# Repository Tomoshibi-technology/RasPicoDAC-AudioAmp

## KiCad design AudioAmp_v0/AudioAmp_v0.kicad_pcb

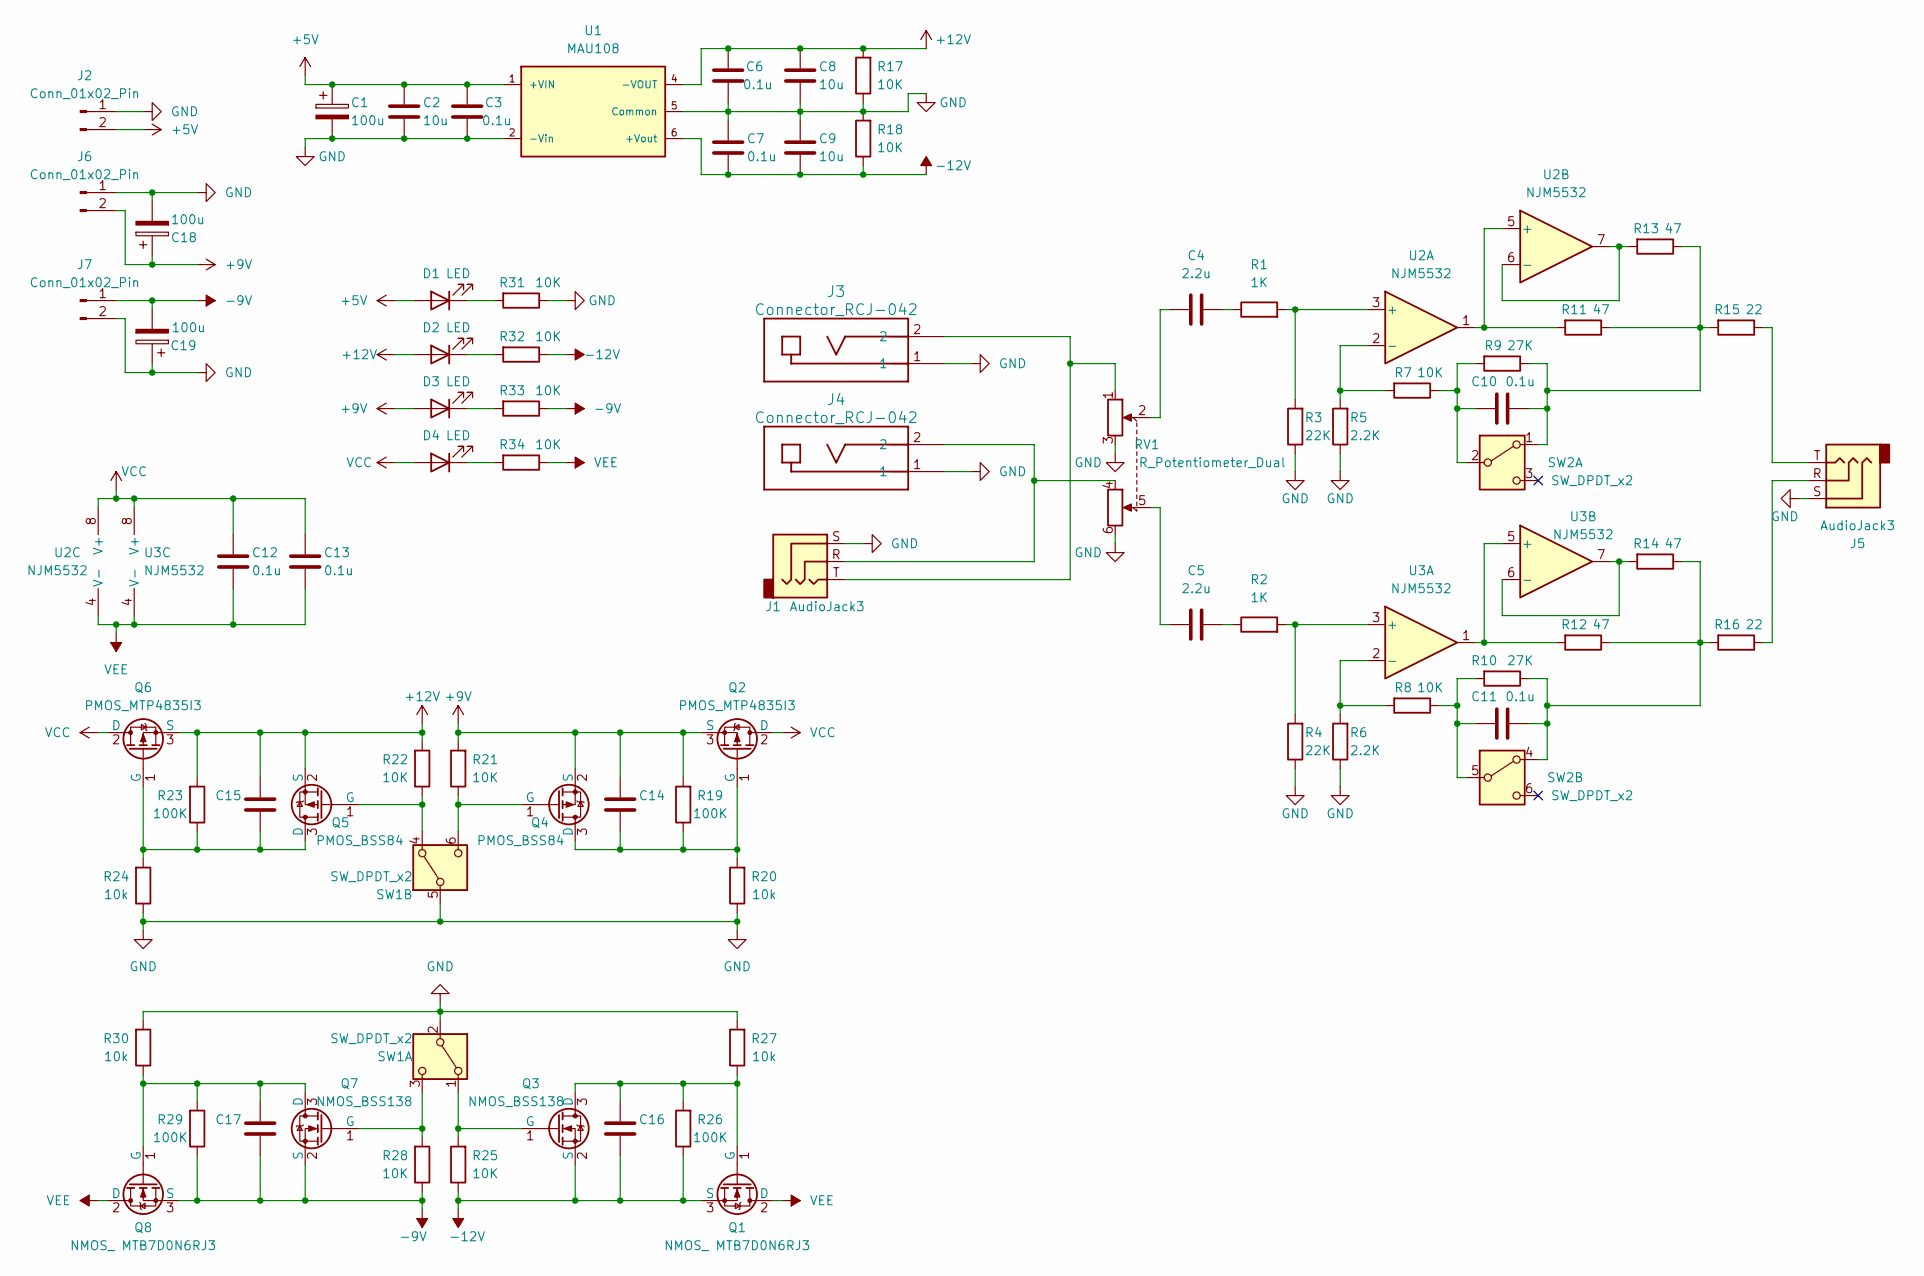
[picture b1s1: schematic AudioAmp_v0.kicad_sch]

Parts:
C1, C18, C19: 100u; CP_Elec_6.3x5.7
C2, C8, C9: 10u; C_0805_2012Metric
C3, C6, C7, C12, C13: 0.1u; C_0603_1608Metric
C4, C5: 2.2u; C_Axial_L17.0mm_D7.0mm_P20.00mm_Horizontal
C10, C11: 0.1u; C_Rect_L13.0mm_W6.0mm_P10.00mm_FKS3_FKP3_MKS4
C14, C15, C16, C17: C_0805_2012Metric
D1, D2, D3, D4: LED; LED_D3.0mm
J1, J5: AudioJack3; Jack_3.5mm_Switronic_ST-005-G_horizontal
J2: Conn_01x02_Pin; Molex_SPOX_5268-02A_1x02_P2.50mm_Horizontal
J3, J4: Connector_RCJ-042; Connector_RCJ-042CUD
J6, J7: Conn_01x02_Pin; JST_XH_S2B-XH-A_1x02_P2.50mm_Horizontal
Q1, Q8: NMOS_ MTB7D0N6RJ3; TO-252-2
Q2, Q6: PMOS_MTP4835I3; TO-252-2
Q3, Q7: NMOS_BSS138; SOT-23
Q4, Q5: PMOS_BSS84; TSOT-23
R1, R2: 1K; R_Axial_DIN0207_L6.3mm_D2.5mm_P10.16mm_Horizontal
R3, R4: 22K; R_Axial_DIN0207_L6.3mm_D2.5mm_P10.16mm_Horizontal
R5, R6: 2.2K; R_Axial_DIN0207_L6.3mm_D2.5mm_P10.16mm_Horizontal
R7, R8, R31, R32, R33, R34: 10K; R_Axial_DIN0207_L6.3mm_D2.5mm_P10.16mm_Horizontal
R9, R10: 27K; R_Axial_DIN0207_L6.3mm_D2.5mm_P10.16mm_Horizontal
R11, R12, R13, R14: 47; R_Axial_DIN0207_L6.3mm_D2.5mm_P10.16mm_Horizontal
R15, R16: 22; R_Axial_DIN0207_L6.3mm_D2.5mm_P10.16mm_Horizontal
R17, R18, R21, R22, R25, R28: 10K; R_0603_1608Metric
R19, R23, R26, R29: 100K; R_0603_1608Metric
R20, R24, R27, R30: 10k; R_0603_1608Metric
RV1: R_Potentiometer_Dual; VR_ALPS9-dual
SW1: SW_DPDT_x2; SW_CK_JS202011CQN_DPDT_Straight
SW2: SW_DPDT_x2; SW_E-Switch_EG2219_DPDT_Angled
U1: MAU108; DCDC_MAUseries; MOUSER_PART_NUMBER 580-OKL-T/6-W12N-C
U2, U3: NJM5532; DIP-8_W7.62mm

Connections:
+5V: C1.1, C2.1, C3.1, D1.2 (A), J2.2, U1.1 (+VIN)
+9V: C14.1, C18.1, D3.2 (A), J6.2, Q2.3 (S), Q4.2 (S), R19.2, R21.2
+12V: C6.1, C8.1, C15.1, D2.2 (A), Q5.2 (S), Q6.3 (S), R17.2, R22.2, R23.2, U1.4 (-VOUT)
-9V: C17.2, C19.2, J7.1, Q7.2 (S), Q8.3 (S), R28.1, R29.1, R33.1
-12V: C7.2, C9.2, C16.2, Q1.3 (S), Q3.2 (S), R18.1, R25.1, R26.1, R32.1, U1.6 (+Vout)
GND: C1.2, C2.2, C3.2, C6.2, C7.1, C8.2, C9.1, C18.2, C19.1, J1.S, J2.1, J3.1, J4.1, J5.S, J6.1, J7.2, R3.1, R4.1, R5.1, R6.1, R17.1, R18.2, R20.1, R24.1, R27.2, R30.2, R31.1, RV1.3, RV1.6, SW1.2 (B), SW1.5 (B), U1.2 (-Vin), U1.5 (Common)
unnamed: C4.1, RV1.2
unnamed: C4.2, R1.1
unnamed: C5.1, RV1.5
unnamed: C5.2, R2.1
unnamed: D1.1 (K), R31.2
unnamed: D2.1 (K), R32.2
unnamed: D3.1 (K), R33.2
unnamed: D4.1 (K), R34.2
unnamed: J1.R, J4.2, RV1.4
unnamed: J1.T, J3.2, RV1.1
unnamed: J5.R, R16.1
unnamed: J5.T, R15.1
unnamed: C16.1, Q1.1 (G), Q3.3 (D), R26.2, R27.1
unnamed: C14.2, Q2.1 (G), Q4.3 (D), R19.1, R20.2
unnamed: Q3.1 (G), R25.2, SW1.1 (A)
unnamed: Q4.1 (G), R21.1, SW1.6 (C)
unnamed: C15.2, Q5.3 (D), Q6.1 (G), R23.1, R24.2
unnamed: Q5.1 (G), R22.1, SW1.4 (A)
unnamed: C17.1, Q7.3 (D), Q8.1 (G), R29.2, R30.1
unnamed: Q7.1 (G), R28.2, SW1.3 (C)
unnamed: C10.2, R9.1, R11.1, R13.1, R15.2, SW2.1 (A)
unnamed: C10.1, R7.1, R9.2, SW2.2 (B)
unnamed: C11.2, R10.1, R12.1, R14.1, R16.2, SW2.4 (A)
unnamed: C11.1, R8.1, R10.2, SW2.5 (B)
unnamed: R1.2, R3.2, U2.3 (+)
unnamed: R5.2, R7.2, U2.2 (-)
unnamed: R11.2, U2.1, U2.5 (+)
unnamed: R13.2, U2.6 (-), U2.7
unnamed: R2.2, R4.2, U3.3 (+)
unnamed: R6.2, R8.2, U3.2 (-)
unnamed: R12.2, U3.1, U3.5 (+)
unnamed: R14.2, U3.6 (-), U3.7
VCC: C12.1, C13.1, D4.2 (A), Q2.2 (D), Q6.2 (D), U2.8 (V+), U3.8 (V+)
VEE: C12.2, C13.2, Q1.2 (D), Q8.2 (D), R34.1, U2.4 (V-), U3.4 (V-)

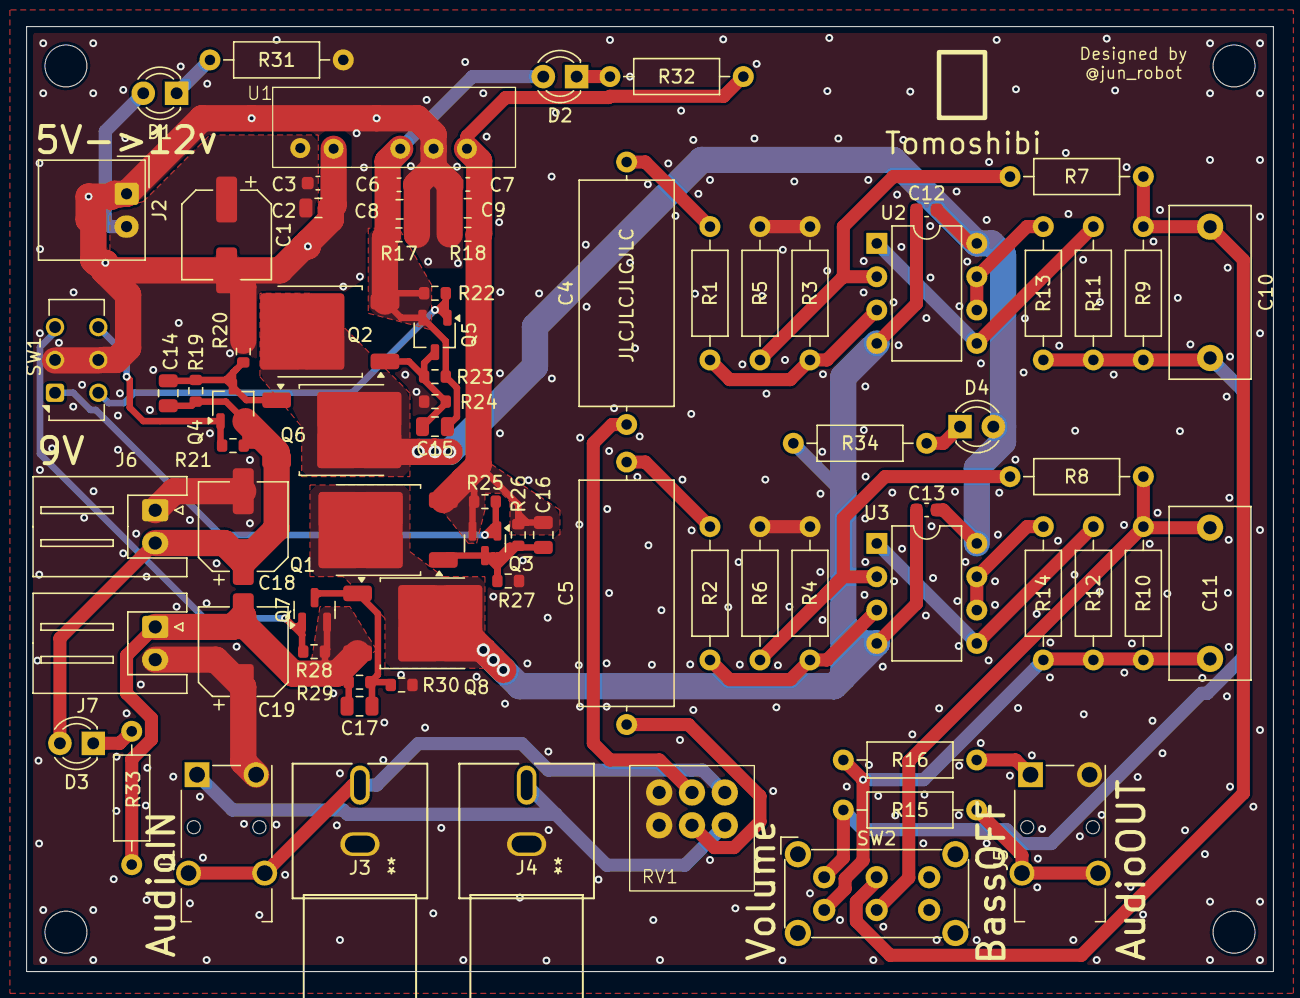
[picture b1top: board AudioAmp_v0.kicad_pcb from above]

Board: 2 copper layers, 95.0 x 72.0 mm, 78 parts (0 on the bottom side), 40 nets.

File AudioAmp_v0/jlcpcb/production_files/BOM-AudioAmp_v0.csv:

Comment,Designator,Footprint,LCSC,Quantity
10K,R22,R_0603_1608Metric,,1
LED,D3,LED_D3.0mm,,1
10K,R33,R_Axial_DIN0207_L6.3mm_D2.5mm_P10.16mm_Horizontal,,1
Conn_01x02_Pin,J6,JST_XH_S2B-XH-A_1x02_P2.50mm_Horizontal,,1
2.2u,C5,C_Axial_L17.0mm_D7.0mm_P20.00mm_Horizontal,,1
Conn_01x02_Pin,J7,JST_XH_S2B-XH-A_1x02_P2.50mm_Horizontal,,1
0.1u,C11,C_Rect_L13.0mm_W6.0mm_P10.00mm_FKS3_FKP3_MKS4,,1
NMOS_BSS138,Q7,SOT-23,,1
0.1u,C7,C_0603_1608Metric,,1
LED,D1,LED_D3.0mm,,1
1K,R2,R_Axial_DIN0207_L6.3mm_D2.5mm_P10.16mm_Horizontal,,1
22K,R3,R_Axial_DIN0207_L6.3mm_D2.5mm_P10.16mm_Horizontal,,1
1K,R1,R_Axial_DIN0207_L6.3mm_D2.5mm_P10.16mm_Horizontal,,1
10k,R27,R_0603_1608Metric,,1
0.1u,C6,C_0603_1608Metric,,1
10K,R8,R_Axial_DIN0207_L6.3mm_D2.5mm_P10.16mm_Horizontal,,1
NMOS_ MTB7D0N6RJ3,Q1,TO-252-2,,1
NJM5532,U2,DIP-8_W7.62mm,,1
10K,R17,R_0603_1608Metric,,1
100u,C1,CP_Elec_6.3x5.7,,1
~,C14,C_0805_2012Metric,,1
22K,R4,R_Axial_DIN0207_L6.3mm_D2.5mm_P10.16mm_Horizontal,,1
10k,R24,R_0603_1608Metric,,1
47,R11,R_Axial_DIN0207_L6.3mm_D2.5mm_P10.16mm_Horizontal,,1
PMOS_BSS84,Q4,TSOT-23,,1
10k,R30,R_0603_1608Metric,,1
10K,R28,R_0603_1608Metric,,1
10K,R25,R_0603_1608Metric,,1
Connector_RCJ-042,J3,Connector_RCJ-042CUD,,1
10K,R31,R_Axial_DIN0207_L6.3mm_D2.5mm_P10.16mm_Horizontal,,1
100u,C19,CP_Elec_6.3x5.7,,1
10K,R32,R_Axial_DIN0207_L6.3mm_D2.5mm_P10.16mm_Horizontal,,1
~,C15,C_0805_2012Metric,,1
MAU108,U1,DCDC_MAUseries,,1
AudioJack3,J5,Jack_3.5mm_Switronic_ST-005-G_horizontal,,1
R_Potentiometer_Dual,RV1,VR_ALPS9-dual,,1
10u,C8,C_0805_2012Metric,,1
27K,R9,R_Axial_DIN0207_L6.3mm_D2.5mm_P10.16mm_Horizontal,,1
100u,C18,CP_Elec_6.3x5.7,,1
0.1u,C12,C_0603_1608Metric,,1
~,C17,C_0805_2012Metric,,1
SW_DPDT_x2,SW1,SW_CK_JS202011CQN_DPDT_Straight,,1
0.1u,C13,C_0603_1608Metric,,1
10u,C2,C_0805_2012Metric,,1
Conn_01x02_Pin,J2,Molex_SPOX_5268-02A_1x02_P2.50mm_Horizontal,,1
LED,D2,LED_D3.0mm,,1
100K,R19,R_0603_1608Metric,,1
0.1u,C10,C_Rect_L13.0mm_W6.0mm_P10.00mm_FKS3_FKP3_MKS4,,1
NMOS_BSS138,Q3,SOT-23,,1
10K,R18,R_0603_1608Metric,,1
PMOS_MTP4835I3,Q2,TO-252-2,,1
10K,R21,R_0603_1608Metric,,1
2.2K,R6,R_Axial_DIN0207_L6.3mm_D2.5mm_P10.16mm_Horizontal,,1
PMOS_MTP4835I3,Q6,TO-252-2,,1
47,R12,R_Axial_DIN0207_L6.3mm_D2.5mm_P10.16mm_Horizontal,,1
27K,R10,R_Axial_DIN0207_L6.3mm_D2.5mm_P10.16mm_Horizontal,,1
NJM5532,U3,DIP-8_W7.62mm,,1
Connector_RCJ-042,J4,Connector_RCJ-042CUD,,1
10K,R7,R_Axial_DIN0207_L6.3mm_D2.5mm_P10.16mm_Horizontal,,1
22,R15,R_Axial_DIN0207_L6.3mm_D2.5mm_P10.16mm_Horizontal,,1
PMOS_BSS84,Q5,TSOT-23,,1
0.1u,C3,C_0603_1608Metric,,1
AudioJack3,J1,Jack_3.5mm_Switronic_ST-005-G_horizontal,,1
47,R13,R_Axial_DIN0207_L6.3mm_D2.5mm_P10.16mm_Horizontal,,1
2.2K,R5,R_Axial_DIN0207_L6.3mm_D2.5mm_P10.16mm_Horizontal,,1
10K,R34,R_Axial_DIN0207_L6.3mm_D2.5mm_P10.16mm_Horizontal,,1
100K,R29,R_0603_1608Metric,,1
2.2u,C4,C_Axial_L17.0mm_D7.0mm_P20.00mm_Horizontal,,1
22,R16,R_Axial_DIN0207_L6.3mm_D2.5mm_P10.16mm_Horizontal,,1
100K,R26,R_0603_1608Metric,,1
47,R14,R_Axial_DIN0207_L6.3mm_D2.5mm_P10.16mm_Horizontal,,1
100K,R23,R_0603_1608Metric,,1
10u,C9,C_0805_2012Metric,,1
SW_DPDT_x2,SW2,SW_E-Switch_EG2219_DPDT_Angled,,1
10k,R20,R_0603_1608Metric,,1
~,C16,C_0805_2012Metric,,1
LED,D4,LED_D3.0mm,,1
NMOS_ MTB7D0N6RJ3,Q8,TO-252-2,,1

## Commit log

2024-11-15 gitignore作成
2024-11-15 一旦おけ
2024-11-15 mainプロジェクトスタート
2024-11-22 名前変更
2024-11-22 電源回路完成
2024-11-22 gitignore更新
2024-11-22 アンプ回路ちょっと
2024-11-22 アンプ回路一応完成
2024-11-26 電源切り替え回路を追加
2024-11-26 電源切り替え回路完成
2024-11-26 基板サイズ確定（秋月B基板互換）
2024-11-28 最低限完成
2024-11-28 LED追加
2024-11-28 シルク追加
2024-11-28 電源切り替えスイッチ修正
2024-11-28 スイッチの方向修正
2024-11-29 ビア打ち
2024-11-29 ビア打ちます
2024-12-01 ビアを増やしたり
2024-12-01 三角波がでた
